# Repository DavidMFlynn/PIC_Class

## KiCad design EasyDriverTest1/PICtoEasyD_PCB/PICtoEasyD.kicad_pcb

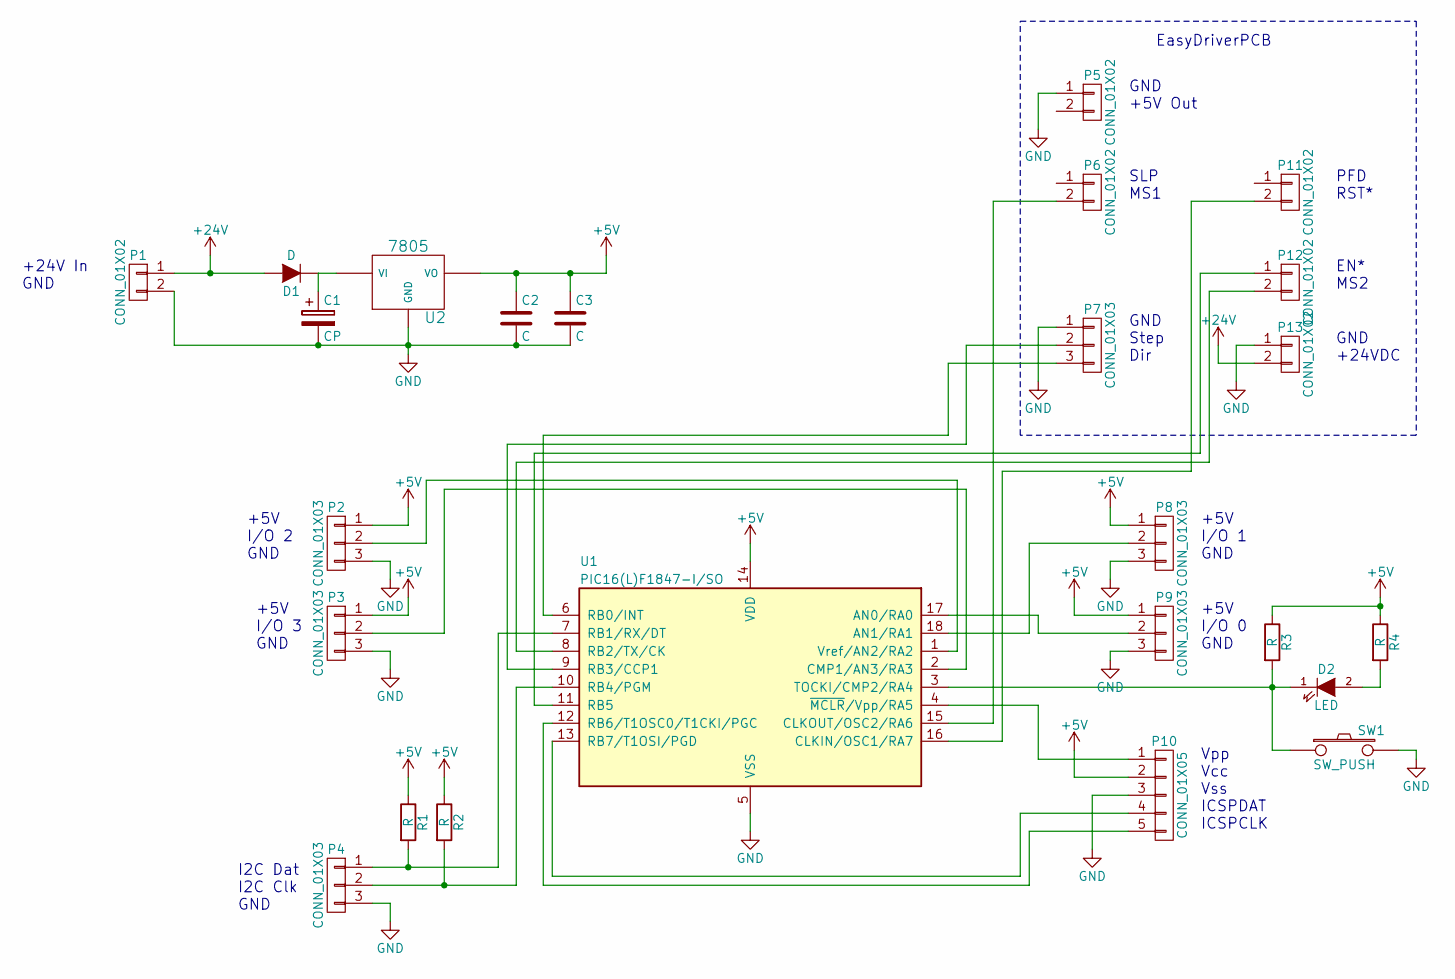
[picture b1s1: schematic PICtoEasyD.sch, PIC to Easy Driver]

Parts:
C1: CP; Elko_vert_11x5mm_RM2.5
C2, C3: C; C_0805_HandSoldering
D1: D; SMA_Handsoldering
D2: LED; LED-1206
P1, P5, P6, P11, P12, P13: CONN_01X02; Pin_Header_Straight_1x02
P2, P3, P4, P7, P8, P9: CONN_01X03; Pin_Header_Straight_1x03
P10: CONN_01X05; Pin_Header_Straight_1x05
R1, R2, R3, R4: R; R_0805_HandSoldering
SW1: SW_PUSH; SW_SPST_PTS645
U1: PIC16(L)F1847-I/SO; SOIC-18_7.5x11.6mm_Pitch1.27mm
U2: 7805; TO-220_Neutral123_Vertical_LargePads

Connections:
+5V: C2.1, C3.1, P2.1, P3.1, P8.1, P9.1, P10.2, R1.1, R2.1, R3.1, R4.1, U1.14 (VDD), U2.VO
+24V: D1.2 (A), P1.1, P13.2
GND: C1.2, C2.2, C3.2, P1.2, P2.3, P3.3, P4.3, P5.1, P7.1, P8.3, P9.3, P10.3, P13.1, SW1.2, U1.5 (VSS), U2.GND
unnamed: C1.1, D1.1 (K), U2.VI
unnamed: D2.1 (K), R3.2, SW1.1, U1.3 (TOCKI/CMP2/RA4)
unnamed: D2.2 (A), R4.2
unnamed: P2.2, U1.1 (Vref/AN2/RA2)
unnamed: P3.2, U1.2 (CMP1/AN3/RA3)
unnamed: P4.1, R1.2, U1.7 (RB1/RX/DT)
unnamed: P4.2, R2.2, U1.10 (RB4/PGM)
unnamed: P6.2, U1.15 (CLKOUT/OSC2/RA6)
unnamed: P7.2, U1.9 (RB3/CCP1)
unnamed: P7.3, U1.6 (RB0/INT)
unnamed: P8.2, U1.18 (AN1/RA1)
unnamed: P9.2, U1.17 (AN0/RA0)
unnamed: P10.1, U1.4 (~MCLR~/Vpp/RA5)
unnamed: P10.4, U1.13 (RB7/T1OSI/PGD)
unnamed: P10.5, U1.12 (RB6/T1OSC0/T1CKI/PGC)
unnamed: P11.2, U1.16 (CLKIN/OSC1/RA7)
unnamed: P12.1, U1.11 (RB5)
unnamed: P12.2, U1.8 (RB2/TX/CK)

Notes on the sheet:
PFD RST*
EN* MS2
GND +24VDC
SLP MS1
GND +5V Out
GND Step Dir
EasyDriverPCB
Vpp Vcc Vss ICSPDAT ICSPCLK
+5V I/O 0 GND
+5V I/O 1 GND
+5V I/O 2 GND
+5V I/O 3 GND
I2C Dat I2C Clk GND
+24V In GND

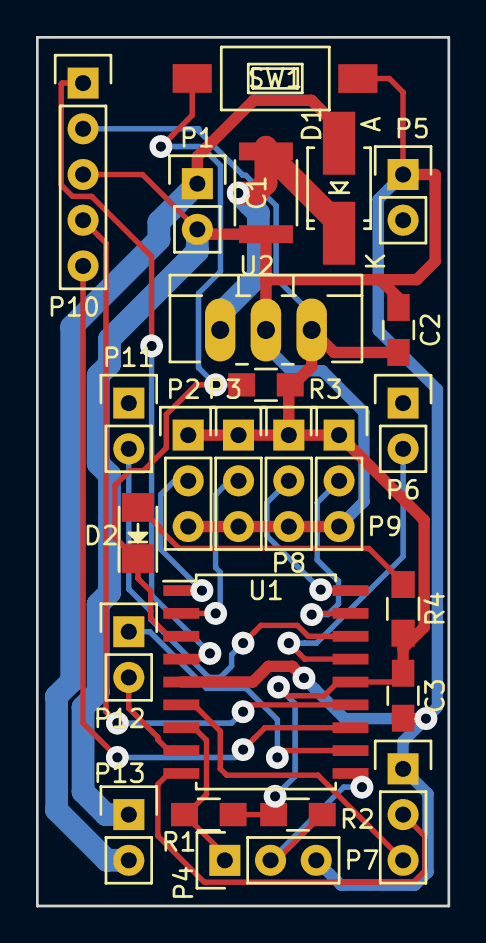
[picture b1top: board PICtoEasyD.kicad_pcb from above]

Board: 2 copper layers, 22.9 x 48.3 mm, 25 parts (0 on the bottom side), 21 nets.

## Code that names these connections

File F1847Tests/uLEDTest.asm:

;====================================================================================================
;
;    Filename:      uLEDTest.asm
;    Date:          4/1/2015
;    File Version:  1.0
;
;    Author:        David M. Flynn
;    Company:       Oxford V.U.E., Inc.
;    E-Mail:        dflynn@oxfordvue.com
;    Web Site:      http://www.oxfordvue.com/
;
;====================================================================================================
;    History:
;
; 1.0   4/1/2015	Simple LED blinker. This program sets all pins to outputs and makes them blink.
;	Every pin except RA5 which is an input only pin blinks.
;
;====================================================================================================
;====================================================================================================
;
;   Pin 1 (RA2/AN2) 
;   Pin 2 (RA3/AN3) 
;   Pin 3 (RA4/AN4) 
;   Pin 4 (RA5/MCLR*) 
;   Pin 5 (GND) Ground
;   Pin 6 (RB0) 
;   Pin 7 (RB1/AN11/SDA1) 
;   Pin 8 (RB2/AN10/RX) 
;   Pin 9 (RB3/CCP1) 
;
;   Pin 10 (RB4/AN8/SLC1) 
;   Pin 11 (RB5/AN7) 
;   Pin 12 (RB6/AN5/CCP2)
;   Pin 13 (RB7/AN6)
;   Pin 14 (Vcc) +5 volts
;   Pin 15 (RA6)
;   Pin 16 (RA7) 
;   Pin 17 (RA0)
;   Pin 18 (RA1)
;
;====================================================================================================
;
;
	list	p=16f1847,r=hex,W=0	; list directive to define processor
	nolist
	include	p16f1847.inc	; processor specific variable definitions
	list
;
	__CONFIG _CONFIG1,_FOSC_INTOSC & _WDTE_OFF & _MCLRE_OFF & _IESO_OFF
;
;
; INTOSC oscillator: I/O function on CLKIN pin
; WDT disabled
; PWRT disabled
; MCLR/VPP pin function is digital input
; Program memory code protection is disabled
; Data memory code protection is disabled
; Brown-out Reset enabled
; CLKOUT function is disabled. I/O or oscillator function on the CLKOUT pin
; Internal/External Switchover mode is disabled
; Fail-Safe Clock Monitor is enabled
;
	__CONFIG _CONFIG2,_WRT_OFF & _PLLEN_OFF & _LVP_OFF
;
; Write protection off
; 4x PLL disabled
; Stack Overflow or Underflow will cause a Reset
; Brown-out Reset Voltage (Vbor), low trip point selected.
; Low-voltage programming enabled
;
; '__CONFIG' directive is used to embed configuration data within .asm file.
; The lables following the directive are located in the respective .inc file.
; See respective data sheet for additional information on configuration word.
;
	constant	oldCode=0
	constant	useRS232=0
;
#Define	_C	STATUS,C
#Define	_Z	STATUS,Z
;========================================================================================
;================================================================================================
;***** VARIABLE DEFINITIONS
; there are 256 bytes of ram, Bank0 0x20..0x7F, Bank1 0xA0..0xEF, Bank2 0x120..0x16F
; there are 256 bytes of EEPROM starting at 0x00 the EEPROM is not mapped into memory but
;  accessed through the EEADR and EEDATA registers
;================================================================================================
;  Bank0 Ram 020h-06Fh 80 Bytes
;
Bank0_Vars	udata	0x20 
;
;
;=======================================================================================================
;  Common Ram 70-7F same for all banks
;      except for ISR_W_Temp these are used for paramiter passing and temp vars
;=======================================================================================================
;
	cblock	0x70
	Param70
	Param71
	Param72
	Param73
	Param74
	Param75
	Param76
	Param77
	Param78
	Param79
	Param7A
	Param7B
	Param7C
	Param7D
	Param7E
	Param7F
	endc
;
;==============================================================================================
;============================================================================================
;
;
	ORG	0x000	; processor reset vector
	CLRF	STATUS
	CLRF	PCLATH
  	goto	start	; go to beginning of program
;
;===============================================================================================
; Interupt Service Routine
;
; we loop through the interupt service routing every 0.008192 seconds
;
;
	ORG	0x004	; interrupt vector location
	CLRF	BSR	; bank0
;
;
;-----------------------------------------------------------------
;
	retfie		; return from interrupt
;
;
;==============================================================================================
;==============================================================================================
;
start	MOVLB	0x01	; select bank 1
	bsf	OPTION_REG,NOT_WPUEN	; disable pullups on port B
	bcf	OPTION_REG,TMR0CS	; TMR0 clock Fosc/4
	bcf	OPTION_REG,PSA	; prescaler assigned to TMR0
	bsf	OPTION_REG,PS0	;111 8mhz/4/256=7812.5hz=128uS/Ct=0.032768S/ISR
	bsf	OPTION_REG,PS1	;101 8mhz/4/64=31250hz=32uS/Ct=0.008192S/ISR
	bsf	OPTION_REG,PS2
;
	MOVLB	0x01	; bank 1
	MOVLW	b'01110000'
	MOVWF	OSCCON
	movlw	b'00010111'	; WDT prescaler 1:65536 period is 2 sec (RESET value)
	movwf	WDTCON 	
;	
	MOVLB	0x03	; bank 3
	CLRF	ANSELA	;Digital I/O
	CLRF	ANSELB	;Digital I/O
;
	MOVLB	0x00	;Bank 0
; setup data ports
	MOVLW	0xFF
	MOVWF	PORTB	;init port B
	MOVWF	PORTA
	MOVLB	0x01	; bank 1
	CLRF	TRISA
	CLRF	TRISB
;
	MOVLB	0x02
;
;=========================================================================================
;=========================================================================================
;  Main Loop
;
;=========================================================================================
MainLoop	CLRWDT
;
	MOVLW	0xFF
	XORWF	LATA,F
	XORWF	LATB,F
;
Loop1	NOP
	DECFSZ	Param78,F
	GOTO	Loop1
	DECFSZ	Param79,F
	GOTO	Loop1
;
	goto	MainLoop
;
;=========================================================================================
;=========================================================================================

;
;
	END
;

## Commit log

2015-03-12 Stepping faster
2015-03-24 Interrupt on change
2015-04-01 Added a simple blink test for the F1847
2015-04-26 Added an I2C example
    2 chips, 2 switches, 2 LEDs a good start
2015-08-20 I2C sample code update
2015-09-08 Update addressing
2016-05-03 Updated I2C
    Added EasyDriverTest firmware and PCB
2016-05-03 Added SerialTest1
